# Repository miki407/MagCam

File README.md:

# MagCam

## Introduction
MagCam is a project that aims to bring a better way of teaching principles of magnetism in a classroom environment. Using this device we hope that students will be more engaged in learning about various topics regarding magnetism as well as electromagnetism. During the process of making this device we looked for a way to improve on the traditional methods of displaying magnetic fields.  

## Comparison with traditional methods

|  Method | Presentation | Versatility | Sensitivity | Polarity | Extra Notes |
|---------|--------------|-------------|-------------|----------| ----------- |
| MagCam  | The results can be displayed on a projector | Very versatile in terms of experiments that can be performed | Sensitive to small magnetic fields but limited by the ADC and pre-amp | Has the ability to distinguish between **north** and **south** poles | Can record the data captured
| Iron Dust | Limited number of students can see the results at one time | Number of experiments that can be performed is limited | Only sensitive to strong magnetic fields. Better results can be achieved if particles are suspended in liquid | Doesn't have a way to clearly distinguish between 2 poles | Can stick to the magnets and damage other equipment in the lab |  
| [Flux Detector](https://www.supermagnete.de/eng/school-magnets/flux-detector-small_M-04) | Limited number of students can see the results at one time | Number of experiments that can be performed is sufficient for basic needs | Only sensitive to strong magnetic fields | Doesn't have a way to clearly distinguish between 2 poles |
| Compass array | Limited number of students can see the results at one time |  Very versatile in terms of experiments that can be performed | Sensitive to weak magnetic fields | Has the ability to distinguish between **north** and **south** poles | The device is composed of mechanical compasses and thus needs to be kept horizontal |
| Ferro fluid | Limited number of students can see the results at one time | Number of experiments that can be performed is sufficient for basic needs | Only sensitive to strong magnetic fields | Doesn't have a way to clearly distinguish between 2 poles | Has the possibility to damage other equipment and is hard to clean |
| Virtual demonstration | The results can be displayed on a projector | Any experiment that can be virtually modeled can be performed | The most sensitive option | Has the ability to distinguish between **north** and **south** poles | Requires special training in use of simulation software. It can take a long time for results to be ready. This method doesn't measure magnetic fields and only **simulates** them |

## Basic overview 
MagCam uses 256 hall effect sensors to determine the strength of the magnetic field over a detection area of 110x110 mm. This data is read and sent to the computer for further processing by and esp32 microcontroller. The data is processed and displayed on the computer using an app that was written specifically for this device.

## App
The app reads the values sent by the esp32 and decodes them into individual frames. This data is then calibrated using a baseline value for each sensors. This improves the reading accuracy and allows for less noisy results. In case large gain is used the values received from the device can be averaged. This allows for even less noisy results. 
The app also has a feature that recreates the magnetic field lines from the change in local magnet field strength.
> App is still in development  and more features are planned in the future. There are also plans to improve the gui

## Files
all the files can be found [here](https://github.com/miki407/MagCam)

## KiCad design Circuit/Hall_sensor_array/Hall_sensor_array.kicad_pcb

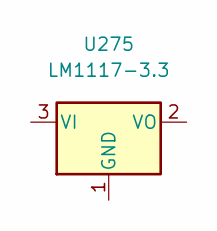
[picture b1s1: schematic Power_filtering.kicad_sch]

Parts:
U275: LM1117-3.3

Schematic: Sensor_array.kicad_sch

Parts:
C1, C2, C3, C4, C5, C6, C7, C8, C9, C10, C11, C12, C13, C14, C15, C16, C17, C18, C19, C20, C21, C22, C23, C24, C25, C26, C27, C28, C29, C30, C31, C32, C33, C34, C35, C36, C37, C38, C39, C40, C41, C42, C43, C44, C45, C46, C47, C48, C49, C50, C51, C52, C53, C54, C55, C56, C57, C58, C59, C60, C61, C62, C63, C64, C65, C66, C67, C68, C69, C70, C71, C72, C73, C74, C75, C76, C77, C78, C79, C80, C81, C82, C83, C84, C85, C86, C87, C88, C89, C90, C91, C92, C93, C94, C95, C96, C97, C98, C99, C100, C101, C102, C103, C104, C105, C106, C107, C108, C109, C110, C111, C112, C113, C114, C115, C116, C117, C118, C119, C120, C121, C122, C123, C124, C125, C126, C127, C128, C129, C130, C131, C132, C133, C134, C135, C136, C137, C138, C139, C140, C141, C142, C143, C144, C145, C146, C147, C148, C149, C150, C151, C152, C153, C154, C155, C156, C157, C158, C159, C160, C161, C162, C163, C164, C165, C166, C167, C168, C169, C170, C171, C172, C173, C174, C175, C176, C177, C178, C179, C180, C181, C182, C183, C184, C185, C186, C187, C188, C189, C190, C191, C192, C193, C194, C195, C196, C197, C198, C199, C200, C201, C202, C203, C204, C205, C206, C207, C208, C209, C210, C211, C212, C213, C214, C215, C216, C217, C218, C219, C220, C221, C222, C223, C224, C225, C226, C227, C228, C229, C230, C231, C232, C233, C234, C235, C236, C237, C238, C239, C240, C241, C242, C243, C244, C245, C246, C247, C248, C249, C250, C251, C252, C253, C254, C255, C256: 100p; C_0603_1608Metric
U1, U2, U3, U4, U5, U6, U7, U8, U9, U10, U11, U12, U13, U14, U15, U16, U17, U18, U19, U20, U21, U22, U23, U24, U25, U26, U27, U28, U29, U30, U31, U32, U33, U34, U35, U36, U37, U38, U39, U40, U41, U42, U43, U44, U45, U46, U47, U48, U49, U50, U51, U52, U53, U54, U55, U56, U57, U58, U59, U60, U61, U62, U63, U64, U65, U66, U67, U68, U69, U70, U71, U72, U73, U74, U75, U76, U77, U78, U79, U80, U81, U82, U83, U84, U85, U86, U87, U88, U89, U90, U91, U92, U93, U94, U95, U96, U97, U98, U99, U100, U101, U102, U103, U104, U105, U106, U107, U108, U109, U110, U111, U112, U113, U114, U115, U116, U117, U118, U119, U120, U121, U122, U123, U124, U125, U126, U127, U128, U129, U130, U131, U132, U133, U134, U135, U136, U137, U138, U139, U140, U141, U142, U143, U144, U145, U146, U147, U148, U149, U150, U151, U152, U153, U154, U155, U156, U157, U158, U159, U160, U161, U162, U163, U164, U165, U166, U167, U168, U169, U170, U171, U172, U173, U174, U175, U176, U177, U178, U179, U180, U181, U182, U183, U184, U185, U186, U187, U188, U189, U190, U191, U192, U193, U194, U195, U196, U197, U198, U199, U200, U201, U202, U203, U204, U205, U206, U207, U208, U209, U210, U211, U212, U213, U214, U215, U216, U217, U218, U219, U220, U221, U222, U223, U224, U225, U226, U227, U228, U229, U230, U231, U232, U233, U234, U235, U236, U237, U238, U239, U240, U241, U242, U243, U244, U245, U246, U247, U248, U249, U250, U251, U252, U253, U254, U255, U256: AH49HSC; SOT-23-3

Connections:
+3.3V: U1.1 (VDD), U2.1 (VDD), U3.1 (VDD), U4.1 (VDD), U5.1 (VDD), U6.1 (VDD), U7.1 (VDD), U8.1 (VDD), U9.1 (VDD), U10.1 (VDD), U11.1 (VDD), U12.1 (VDD), U13.1 (VDD), U14.1 (VDD), U15.1 (VDD), U16.1 (VDD), U17.1 (VDD), U18.1 (VDD), U19.1 (VDD), U20.1 (VDD), U21.1 (VDD), U22.1 (VDD), U23.1 (VDD), U24.1 (VDD), U25.1 (VDD), U26.1 (VDD), U27.1 (VDD), U28.1 (VDD), U29.1 (VDD), U30.1 (VDD), U31.1 (VDD), U32.1 (VDD), U33.1 (VDD), U34.1 (VDD), U35.1 (VDD), U36.1 (VDD), U37.1 (VDD), U38.1 (VDD), U39.1 (VDD), U40.1 (VDD), U41.1 (VDD), U42.1 (VDD), U43.1 (VDD), U44.1 (VDD), U45.1 (VDD), U46.1 (VDD), U47.1 (VDD), U48.1 (VDD), U49.1 (VDD), U50.1 (VDD), U51.1 (VDD), U52.1 (VDD), U53.1 (VDD), U54.1 (VDD), U55.1 (VDD), U56.1 (VDD), U57.1 (VDD), U58.1 (VDD), U59.1 (VDD), U60.1 (VDD), U61.1 (VDD), U62.1 (VDD), U63.1 (VDD), U64.1 (VDD), U65.1 (VDD), U66.1 (VDD), U67.1 (VDD), U68.1 (VDD), U69.1 (VDD), U70.1 (VDD), U71.1 (VDD), U72.1 (VDD), U73.1 (VDD), U74.1 (VDD), U75.1 (VDD), U76.1 (VDD), U77.1 (VDD), U78.1 (VDD), U79.1 (VDD), U80.1 (VDD), U81.1 (VDD), U82.1 (VDD), U83.1 (VDD), U84.1 (VDD), U85.1 (VDD), U86.1 (VDD), U87.1 (VDD), U88.1 (VDD), U89.1 (VDD), U90.1 (VDD), U91.1 (VDD), U92.1 (VDD), U93.1 (VDD), U94.1 (VDD), U95.1 (VDD), U96.1 (VDD), U97.1 (VDD), U98.1 (VDD), U99.1 (VDD), U100.1 (VDD), U101.1 (VDD), U102.1 (VDD), U103.1 (VDD), U104.1 (VDD), U105.1 (VDD), U106.1 (VDD), U107.1 (VDD), U108.1 (VDD), U109.1 (VDD), U110.1 (VDD), U111.1 (VDD), U112.1 (VDD), U113.1 (VDD), U114.1 (VDD), U115.1 (VDD), U116.1 (VDD), U117.1 (VDD), U118.1 (VDD), U119.1 (VDD), U120.1 (VDD), U121.1 (VDD), U122.1 (VDD), U123.1 (VDD), U124.1 (VDD), U125.1 (VDD), U126.1 (VDD), U127.1 (VDD), U128.1 (VDD), U129.1 (VDD), U130.1 (VDD), U131.1 (VDD), U132.1 (VDD), U133.1 (VDD), U134.1 (VDD), U135.1 (VDD), U136.1 (VDD), U137.1 (VDD), U138.1 (VDD), U139.1 (VDD), U140.1 (VDD), U141.1 (VDD), U142.1 (VDD), U143.1 (VDD), U144.1 (VDD), U145.1 (VDD), U146.1 (VDD), U147.1 (VDD), U148.1 (VDD), U149.1 (VDD), U150.1 (VDD), U151.1 (VDD), U152.1 (VDD), U153.1 (VDD), U154.1 (VDD), U155.1 (VDD), U156.1 (VDD), U157.1 (VDD), U158.1 (VDD), U159.1 (VDD), U160.1 (VDD), U161.1 (VDD), U162.1 (VDD), U163.1 (VDD), U164.1 (VDD), U165.1 (VDD), U166.1 (VDD), U167.1 (VDD), U168.1 (VDD), U169.1 (VDD), U170.1 (VDD), U171.1 (VDD), U172.1 (VDD), U173.1 (VDD), U174.1 (VDD), U175.1 (VDD), U176.1 (VDD), U177.1 (VDD), U178.1 (VDD), U179.1 (VDD), U180.1 (VDD), U181.1 (VDD), U182.1 (VDD), U183.1 (VDD), U184.1 (VDD), U185.1 (VDD), U186.1 (VDD), U187.1 (VDD), U188.1 (VDD), U189.1 (VDD), U190.1 (VDD), U191.1 (VDD), U192.1 (VDD), U193.1 (VDD), U194.1 (VDD), U195.1 (VDD), U196.1 (VDD), U197.1 (VDD), U198.1 (VDD), U199.1 (VDD), U200.1 (VDD), U201.1 (VDD), U202.1 (VDD), U203.1 (VDD), U204.1 (VDD), U205.1 (VDD), U206.1 (VDD), U207.1 (VDD), U208.1 (VDD), U209.1 (VDD), U210.1 (VDD), U211.1 (VDD), U212.1 (VDD), U213.1 (VDD), U214.1 (VDD), U215.1 (VDD), U216.1 (VDD), U217.1 (VDD), U218.1 (VDD), U219.1 (VDD), U220.1 (VDD), U221.1 (VDD), U222.1 (VDD), U223.1 (VDD), U224.1 (VDD), U225.1 (VDD), U226.1 (VDD), U227.1 (VDD), U228.1 (VDD), U229.1 (VDD), U230.1 (VDD), U231.1 (VDD), U232.1 (VDD), U233.1 (VDD), U234.1 (VDD), U235.1 (VDD), U236.1 (VDD), U237.1 (VDD), U238.1 (VDD), U239.1 (VDD), U240.1 (VDD), U241.1 (VDD), U242.1 (VDD), U243.1 (VDD), U244.1 (VDD), U245.1 (VDD), U246.1 (VDD), U247.1 (VDD), U248.1 (VDD), U249.1 (VDD), U250.1 (VDD), U251.1 (VDD), U252.1 (VDD), U253.1 (VDD), U254.1 (VDD), U255.1 (VDD), U256.1 (VDD)
GND: C1.2, C2.2, C3.2, C4.2, C5.2, C6.2, C7.2, C8.2, C9.2, C10.2, C11.2, C12.2, C13.2, C14.2, C15.2, C16.2, C17.2, C18.2, C19.2, C20.2, C21.2, C22.2, C23.2, C24.2, C25.2, C26.2, C27.2, C28.2, C29.2, C30.2, C31.2, C32.2, C33.2, C34.2, C35.2, C36.2, C37.2, C38.2, C39.2, C40.2, C41.2, C42.2, C43.2, C44.2, C45.2, C46.2, C47.2, C48.2, C49.2, C50.2, C51.2, C52.2, C53.2, C54.2, C55.2, C56.2, C57.2, C58.2, C59.2, C60.2, C61.2, C62.2, C63.2, C64.2, C65.2, C66.2, C67.2, C68.2, C69.2, C70.2, C71.2, C72.2, C73.2, C74.2, C75.2, C76.2, C77.2, C78.2, C79.2, C80.2, C81.2, C82.2, C83.2, C84.2, C85.2, C86.2, C87.2, C88.2, C89.2, C90.2, C91.2, C92.2, C93.2, C94.2, C95.2, C96.2, C97.2, C98.2, C99.2, C100.2, C101.2, C102.2, C103.2, C104.2, C105.2, C106.2, C107.2, C108.2, C109.2, C110.2, C111.2, C112.2, C113.2, C114.2, C115.2, C116.2, C117.2, C118.2, C119.2, C120.2, C121.2, C122.2, C123.2, C124.2, C125.2, C126.2, C127.2, C128.2, C129.2, C130.2, C131.2, C132.2, C133.2, C134.2, C135.2, C136.2, C137.2, C138.2, C139.2, C140.2, C141.2, C142.2, C143.2, C144.2, C145.2, C146.2, C147.2, C148.2, C149.2, C150.2, C151.2, C152.2, C153.2, C154.2, C155.2, C156.2, C157.2, C158.2, C159.2, C160.2, C161.2, C162.2, C163.2, C164.2, C165.2, C166.2, C167.2, C168.2, C169.2, C170.2, C171.2, C172.2, C173.2, C174.2, C175.2, C176.2, C177.2, C178.2, C179.2, C180.2, C181.2, C182.2, C183.2, C184.2, C185.2, C186.2, C187.2, C188.2, C189.2, C190.2, C191.2, C192.2, C193.2, C194.2, C195.2, C196.2, C197.2, C198.2, C199.2, C200.2, C201.2, C202.2, C203.2, C204.2, C205.2, C206.2, C207.2, C208.2, C209.2, C210.2, C211.2, C212.2, C213.2, C214.2, C215.2, C216.2, C217.2, C218.2, C219.2, C220.2, C221.2, C222.2, C223.2, C224.2, C225.2, C226.2, C227.2, C228.2, C229.2, C230.2, C231.2, C232.2, C233.2, C234.2, C235.2, C236.2, C237.2, C238.2, C239.2, C240.2, C241.2, C242.2, C243.2, C244.2, C245.2, C246.2, C247.2, C248.2, C249.2, C250.2, C251.2, C252.2, C253.2, C254.2, C255.2, C256.2, U1.3 (GND), U2.3 (GND), U3.3 (GND), U4.3 (GND), U5.3 (GND), U6.3 (GND), U7.3 (GND), U8.3 (GND), U9.3 (GND), U10.3 (GND), U11.3 (GND), U12.3 (GND), U13.3 (GND), U14.3 (GND), U15.3 (GND), U16.3 (GND), U17.3 (GND), U18.3 (GND), U19.3 (GND), U20.3 (GND), U21.3 (GND), U22.3 (GND), U23.3 (GND), U24.3 (GND), U25.3 (GND), U26.3 (GND), U27.3 (GND), U28.3 (GND), U29.3 (GND), U30.3 (GND), U31.3 (GND), U32.3 (GND), U33.3 (GND), U34.3 (GND), U35.3 (GND), U36.3 (GND), U37.3 (GND), U38.3 (GND), U39.3 (GND), U40.3 (GND), U41.3 (GND), U42.3 (GND), U43.3 (GND), U44.3 (GND), U45.3 (GND), U46.3 (GND), U47.3 (GND), U48.3 (GND), U49.3 (GND), U50.3 (GND), U51.3 (GND), U52.3 (GND), U53.3 (GND), U54.3 (GND), U55.3 (GND), U56.3 (GND), U57.3 (GND), U58.3 (GND), U59.3 (GND), U60.3 (GND), U61.3 (GND), U62.3 (GND), U63.3 (GND), U64.3 (GND), U65.3 (GND), U66.3 (GND), U67.3 (GND), U68.3 (GND), U69.3 (GND), U70.3 (GND), U71.3 (GND), U72.3 (GND), U73.3 (GND), U74.3 (GND), U75.3 (GND), U76.3 (GND), U77.3 (GND), U78.3 (GND), U79.3 (GND), U80.3 (GND), U81.3 (GND), U82.3 (GND), U83.3 (GND), U84.3 (GND), U85.3 (GND), U86.3 (GND), U87.3 (GND), U88.3 (GND), U89.3 (GND), U90.3 (GND), U91.3 (GND), U92.3 (GND), U93.3 (GND), U94.3 (GND), U95.3 (GND), U96.3 (GND), U97.3 (GND), U98.3 (GND), U99.3 (GND), U100.3 (GND), U101.3 (GND), U102.3 (GND), U103.3 (GND), U104.3 (GND), U105.3 (GND), U106.3 (GND), U107.3 (GND), U108.3 (GND), U109.3 (GND), U110.3 (GND), U111.3 (GND), U112.3 (GND), U113.3 (GND), U114.3 (GND), U115.3 (GND), U116.3 (GND), U117.3 (GND), U118.3 (GND), U119.3 (GND), U120.3 (GND), U121.3 (GND), U122.3 (GND), U123.3 (GND), U124.3 (GND), U125.3 (GND), U126.3 (GND), U127.3 (GND), U128.3 (GND), U129.3 (GND), U130.3 (GND), U131.3 (GND), U132.3 (GND), U133.3 (GND), U134.3 (GND), U135.3 (GND), U136.3 (GND), U137.3 (GND), U138.3 (GND), U139.3 (GND), U140.3 (GND), U141.3 (GND), U142.3 (GND), U143.3 (GND), U144.3 (GND), U145.3 (GND), U146.3 (GND), U147.3 (GND), U148.3 (GND), U149.3 (GND), U150.3 (GND), U151.3 (GND), U152.3 (GND), U153.3 (GND), U154.3 (GND), U155.3 (GND), U156.3 (GND), U157.3 (GND), U158.3 (GND), U159.3 (GND), U160.3 (GND), U161.3 (GND), U162.3 (GND), U163.3 (GND), U164.3 (GND), U165.3 (GND), U166.3 (GND), U167.3 (GND), U168.3 (GND), U169.3 (GND), U170.3 (GND), U171.3 (GND), U172.3 (GND), U173.3 (GND), U174.3 (GND), U175.3 (GND), U176.3 (GND), U177.3 (GND), U178.3 (GND), U179.3 (GND), U180.3 (GND), U181.3 (GND), U182.3 (GND), U183.3 (GND), U184.3 (GND), U185.3 (GND), U186.3 (GND), U187.3 (GND), U188.3 (GND), U189.3 (GND), U190.3 (GND), U191.3 (GND), U192.3 (GND), U193.3 (GND), U194.3 (GND), U195.3 (GND), U196.3 (GND), U197.3 (GND), U198.3 (GND), U199.3 (GND), U200.3 (GND), U201.3 (GND), U202.3 (GND), U203.3 (GND), U204.3 (GND), U205.3 (GND), U206.3 (GND), U207.3 (GND), U208.3 (GND), U209.3 (GND), U210.3 (GND), U211.3 (GND), U212.3 (GND), U213.3 (GND), U214.3 (GND), U215.3 (GND), U216.3 (GND), U217.3 (GND), U218.3 (GND), U219.3 (GND), U220.3 (GND), U221.3 (GND), U222.3 (GND), U223.3 (GND), U224.3 (GND), U225.3 (GND), U226.3 (GND), U227.3 (GND), U228.3 (GND), U229.3 (GND), U230.3 (GND), U231.3 (GND), U232.3 (GND), U233.3 (GND), U234.3 (GND), U235.3 (GND), U236.3 (GND), U237.3 (GND), U238.3 (GND), U239.3 (GND), U240.3 (GND), U241.3 (GND), U242.3 (GND), U243.3 (GND), U244.3 (GND), U245.3 (GND), U246.3 (GND), U247.3 (GND), U248.3 (GND), U249.3 (GND), U250.3 (GND), U251.3 (GND), U252.3 (GND), U253.3 (GND), U254.3 (GND), U255.3 (GND), U256.3 (GND); also elsewhere on the board
X1Y1: C1.1, U1.2 (OUTPUT); also elsewhere on the board
X1Y2: C2.1, U2.2 (OUTPUT); also elsewhere on the board
X1Y3: C3.1, U3.2 (OUTPUT); also elsewhere on the board
X1Y4: C4.1, U4.2 (OUTPUT); also elsewhere on the board
X1Y5: C5.1, U5.2 (OUTPUT); also elsewhere on the board
X1Y6: C6.1, U6.2 (OUTPUT); also elsewhere on the board
X1Y7: C7.1, U7.2 (OUTPUT); also elsewhere on the board
X1Y8: C8.1, U8.2 (OUTPUT); also elsewhere on the board
X1Y9: C9.1, U9.2 (OUTPUT); also elsewhere on the board
X1Y10: C10.1, U10.2 (OUTPUT); also elsewhere on the board
X1Y11: C11.1, U11.2 (OUTPUT); also elsewhere on the board
X1Y12: C12.1, U12.2 (OUTPUT); also elsewhere on the board
X1Y13: C13.1, U13.2 (OUTPUT); also elsewhere on the board
X1Y14: C14.1, U14.2 (OUTPUT); also elsewhere on the board
X1Y15: C15.1, U15.2 (OUTPUT); also elsewhere on the board
X1Y16: C16.1, U16.2 (OUTPUT); also elsewhere on the board
X2Y1: C17.1, U17.2 (OUTPUT); also elsewhere on the board
X2Y2: C18.1, U18.2 (OUTPUT); also elsewhere on the board
X2Y3: C19.1, U19.2 (OUTPUT); also elsewhere on the board
X2Y4: C20.1, U20.2 (OUTPUT); also elsewhere on the board
X2Y5: C21.1, U21.2 (OUTPUT); also elsewhere on the board
X2Y6: C22.1, U22.2 (OUTPUT); also elsewhere on the board
X2Y7: C23.1, U23.2 (OUTPUT); also elsewhere on the board
X2Y8: C24.1, U24.2 (OUTPUT); also elsewhere on the board
X2Y9: C25.1, U25.2 (OUTPUT); also elsewhere on the board
X2Y10: C26.1, U26.2 (OUTPUT); also elsewhere on the board
X2Y11: C27.1, U27.2 (OUTPUT); also elsewhere on the board
X2Y12: C28.1, U28.2 (OUTPUT); also elsewhere on the board
X2Y13: C29.1, U29.2 (OUTPUT); also elsewhere on the board
X2Y14: C30.1, U30.2 (OUTPUT); also elsewhere on the board
X2Y15: C31.1, U31.2 (OUTPUT); also elsewhere on the board
X2Y16: C32.1, U32.2 (OUTPUT); also elsewhere on the board
X3Y1: C33.1, U33.2 (OUTPUT); also elsewhere on the board
X3Y2: C34.1, U34.2 (OUTPUT); also elsewhere on the board
X3Y3: C35.1, U35.2 (OUTPUT); also elsewhere on the board
X3Y4: C36.1, U36.2 (OUTPUT); also elsewhere on the board
X3Y5: C37.1, U37.2 (OUTPUT); also elsewhere on the board
X3Y6: C38.1, U38.2 (OUTPUT); also elsewhere on the board
X3Y7: C39.1, U39.2 (OUTPUT); also elsewhere on the board
X3Y8: C40.1, U40.2 (OUTPUT); also elsewhere on the board
X3Y9: C41.1, U41.2 (OUTPUT); also elsewhere on the board
X3Y10: C42.1, U42.2 (OUTPUT); also elsewhere on the board
X3Y11: C43.1, U43.2 (OUTPUT); also elsewhere on the board
X3Y12: C44.1, U44.2 (OUTPUT); also elsewhere on the board
X3Y13: C45.1, U45.2 (OUTPUT); also elsewhere on the board
X3Y14: C46.1, U46.2 (OUTPUT); also elsewhere on the board
X3Y15: C47.1, U47.2 (OUTPUT); also elsewhere on the board
X3Y16: C48.1, U48.2 (OUTPUT); also elsewhere on the board
X4Y1: C49.1, U49.2 (OUTPUT); also elsewhere on the board
X4Y2: C50.1, U50.2 (OUTPUT); also elsewhere on the board
X4Y3: C51.1, U51.2 (OUTPUT); also elsewhere on the board
X4Y4: C52.1, U52.2 (OUTPUT); also elsewhere on the board
X4Y5: C53.1, U53.2 (OUTPUT); also elsewhere on the board
X4Y6: C54.1, U54.2 (OUTPUT); also elsewhere on the board
X4Y7: C55.1, U55.2 (OUTPUT); also elsewhere on the board
X4Y8: C56.1, U56.2 (OUTPUT); also elsewhere on the board
X4Y9: C57.1, U57.2 (OUTPUT); also elsewhere on the board
X4Y10: C58.1, U58.2 (OUTPUT); also elsewhere on the board
X4Y11: C59.1, U59.2 (OUTPUT); also elsewhere on the board
X4Y12: C60.1, U60.2 (OUTPUT); also elsewhere on the board
X4Y13: C61.1, U61.2 (OUTPUT); also elsewhere on the board
X4Y14: C62.1, U62.2 (OUTPUT); also elsewhere on the board
X4Y15: C63.1, U63.2 (OUTPUT); also elsewhere on the board
X4Y16: C64.1, U64.2 (OUTPUT); also elsewhere on the board
X5Y1: C65.1, U65.2 (OUTPUT); also elsewhere on the board
X5Y2: C66.1, U66.2 (OUTPUT); also elsewhere on the board
X5Y3: C67.1, U67.2 (OUTPUT); also elsewhere on the board
X5Y4: C68.1, U68.2 (OUTPUT); also elsewhere on the board
X5Y5: C69.1, U69.2 (OUTPUT); also elsewhere on the board
X5Y6: C70.1, U70.2 (OUTPUT); also elsewhere on the board
X5Y7: C71.1, U71.2 (OUTPUT); also elsewhere on the board
X5Y8: C72.1, U72.2 (OUTPUT); also elsewhere on the board
X5Y9: C73.1, U73.2 (OUTPUT); also elsewhere on the board
X5Y10: C74.1, U74.2 (OUTPUT); also elsewhere on the board
X5Y11: C75.1, U75.2 (OUTPUT); also elsewhere on the board
X5Y12: C76.1, U76.2 (OUTPUT); also elsewhere on the board
X5Y13: C77.1, U77.2 (OUTPUT); also elsewhere on the board
X5Y14: C78.1, U78.2 (OUTPUT); also elsewhere on the board
X5Y15: C79.1, U79.2 (OUTPUT); also elsewhere on the board
X5Y16: C80.1, U80.2 (OUTPUT); also elsewhere on the board
X6Y1: C81.1, U81.2 (OUTPUT); also elsewhere on the board
X6Y2: C82.1, U82.2 (OUTPUT); also elsewhere on the board
X6Y3: C83.1, U83.2 (OUTPUT); also elsewhere on the board
X6Y4: C84.1, U84.2 (OUTPUT); also elsewhere on the board
X6Y5: C85.1, U85.2 (OUTPUT); also elsewhere on the board
X6Y6: C86.1, U86.2 (OUTPUT); also elsewhere on the board
X6Y7: C87.1, U87.2 (OUTPUT); also elsewhere on the board
X6Y8: C88.1, U88.2 (OUTPUT); also elsewhere on the board
X6Y9: C89.1, U89.2 (OUTPUT); also elsewhere on the board
X6Y10: C90.1, U90.2 (OUTPUT); also elsewhere on the board
X6Y11: C91.1, U91.2 (OUTPUT); also elsewhere on the board
X6Y12: C92.1, U92.2 (OUTPUT); also elsewhere on the board
X6Y13: C93.1, U93.2 (OUTPUT); also elsewhere on the board
X6Y14: C94.1, U94.2 (OUTPUT); also elsewhere on the board
X6Y15: C95.1, U95.2 (OUTPUT); also elsewhere on the board
X6Y16: C96.1, U96.2 (OUTPUT); also elsewhere on the board
X7Y1: C97.1, U97.2 (OUTPUT); also elsewhere on the board
X7Y2: C98.1, U98.2 (OUTPUT); also elsewhere on the board
X7Y3: C99.1, U99.2 (OUTPUT); also elsewhere on the board
X7Y4: C100.1, U100.2 (OUTPUT); also elsewhere on the board
X7Y5: C101.1, U101.2 (OUTPUT); also elsewhere on the board
X7Y6: C102.1, U102.2 (OUTPUT); also elsewhere on the board
X7Y7: C103.1, U103.2 (OUTPUT); also elsewhere on the board
X7Y8: C104.1, U104.2 (OUTPUT); also elsewhere on the board
X7Y9: C105.1, U105.2 (OUTPUT); also elsewhere on the board
X7Y10: C106.1, U106.2 (OUTPUT); also elsewhere on the board
X7Y11: C107.1, U107.2 (OUTPUT); also elsewhere on the board
X7Y12: C108.1, U108.2 (OUTPUT); also elsewhere on the board
X7Y13: C109.1, U109.2 (OUTPUT); also elsewhere on the board
X7Y14: C110.1, U110.2 (OUTPUT); also elsewhere on the board
X7Y15: C111.1, U111.2 (OUTPUT); also elsewhere on the board
X7Y16: C112.1, U112.2 (OUTPUT); also elsewhere on the board
X8Y1: C113.1, U113.2 (OUTPUT); also elsewhere on the board
X8Y2: C114.1, U114.2 (OUTPUT); also elsewhere on the board
X8Y3: C115.1, U115.2 (OUTPUT); also elsewhere on the board
X8Y4: C116.1, U116.2 (OUTPUT); also elsewhere on the board
X8Y5: C117.1, U117.2 (OUTPUT); also elsewhere on the board
X8Y6: C118.1, U118.2 (OUTPUT); also elsewhere on the board
X8Y7: C119.1, U119.2 (OUTPUT); also elsewhere on the board
X8Y8: C120.1, U120.2 (OUTPUT); also elsewhere on the board
X8Y9: C121.1, U121.2 (OUTPUT); also elsewhere on the board
X8Y10: C122.1, U122.2 (OUTPUT); also elsewhere on the board
X8Y11: C123.1, U123.2 (OUTPUT); also elsewhere on the board
X8Y12: C124.1, U124.2 (OUTPUT); also elsewhere on the board
X8Y13: C125.1, U125.2 (OUTPUT); also elsewhere on the board
X8Y14: C126.1, U126.2 (OUTPUT); also elsewhere on the board
X8Y15: C127.1, U127.2 (OUTPUT); also elsewhere on the board
X8Y16: C128.1, U128.2 (OUTPUT); also elsewhere on the board
X9Y1: C129.1, U129.2 (OUTPUT); also elsewhere on the board
X9Y2: C130.1, U130.2 (OUTPUT); also elsewhere on the board
X9Y3: C131.1, U131.2 (OUTPUT); also elsewhere on the board
X9Y4: C132.1, U132.2 (OUTPUT); also elsewhere on the board
X9Y5: C133.1, U133.2 (OUTPUT); also elsewhere on the board
X9Y6: C134.1, U134.2 (OUTPUT); also elsewhere on the board
X9Y7: C135.1, U135.2 (OUTPUT); also elsewhere on the board
X9Y8: C136.1, U136.2 (OUTPUT); also elsewhere on the board
X9Y9: C137.1, U137.2 (OUTPUT); also elsewhere on the board
X9Y10: C138.1, U138.2 (OUTPUT); also elsewhere on the board
X9Y11: C139.1, U139.2 (OUTPUT); also elsewhere on the board
X9Y12: C140.1, U140.2 (OUTPUT); also elsewhere on the board
X9Y13: C141.1, U141.2 (OUTPUT); also elsewhere on the board
X9Y14: C142.1, U142.2 (OUTPUT); also elsewhere on the board
X9Y15: C143.1, U143.2 (OUTPUT); also elsewhere on the board
X9Y16: C144.1, U144.2 (OUTPUT); also elsewhere on the board
X10Y1: C145.1, U145.2 (OUTPUT); also elsewhere on the board
X10Y2: C146.1, U146.2 (OUTPUT); also elsewhere on the board
X10Y3: C147.1, U147.2 (OUTPUT); also elsewhere on the board
X10Y4: C148.1, U148.2 (OUTPUT); also elsewhere on the board
X10Y5: C149.1, U149.2 (OUTPUT); also elsewhere on the board
X10Y6: C150.1, U150.2 (OUTPUT); also elsewhere on the board
X10Y7: C151.1, U151.2 (OUTPUT); also elsewhere on the board
X10Y8: C152.1, U152.2 (OUTPUT); also elsewhere on the board
X10Y9: C153.1, U153.2 (OUTPUT); also elsewhere on the board
X10Y10: C154.1, U154.2 (OUTPUT); also elsewhere on the board
X10Y11: C155.1, U155.2 (OUTPUT); also elsewhere on the board
X10Y12: C156.1, U156.2 (OUTPUT); also elsewhere on the board
X10Y13: C157.1, U157.2 (OUTPUT); also elsewhere on the board
X10Y14: C158.1, U158.2 (OUTPUT); also elsewhere on the board
X10Y15: C159.1, U159.2 (OUTPUT); also elsewhere on the board
X10Y16: C160.1, U160.2 (OUTPUT); also elsewhere on the board
X11Y1: C161.1, U161.2 (OUTPUT); also elsewhere on the board
X11Y2: C162.1, U162.2 (OUTPUT); also elsewhere on the board
X11Y3: C163.1, U163.2 (OUTPUT); also elsewhere on the board
X11Y4: C164.1, U164.2 (OUTPUT); also elsewhere on the board
X11Y5: C165.1, U165.2 (OUTPUT); also elsewhere on the board
X11Y6: C166.1, U166.2 (OUTPUT); also elsewhere on the board
X11Y7: C167.1, U167.2 (OUTPUT); also elsewhere on the board
X11Y8: C168.1, U168.2 (OUTPUT); also elsewhere on the board
X11Y9: C169.1, U169.2 (OUTPUT); also elsewhere on the board
X11Y10: C170.1, U170.2 (OUTPUT); also elsewhere on the board
X11Y11: C171.1, U171.2 (OUTPUT); also elsewhere on the board
X11Y12: C172.1, U172.2 (OUTPUT); also elsewhere on the board
X11Y13: C173.1, U173.2 (OUTPUT); also elsewhere on the board
X11Y14: C174.1, U174.2 (OUTPUT); also elsewhere on the board
X11Y15: C175.1, U175.2 (OUTPUT); also elsewhere on the board
X11Y16: C176.1, U176.2 (OUTPUT); also elsewhere on the board
X12Y1: C177.1, U177.2 (OUTPUT); also elsewhere on the board
X12Y2: C178.1, U178.2 (OUTPUT); also elsewhere on the board
X12Y3: C179.1, U179.2 (OUTPUT); also elsewhere on the board
X12Y4: C180.1, U180.2 (OUTPUT); also elsewhere on the board
X12Y5: C181.1, U181.2 (OUTPUT); also elsewhere on the board
X12Y6: C182.1, U182.2 (OUTPUT); also elsewhere on the board
X12Y7: C183.1, U183.2 (OUTPUT); also elsewhere on the board
X12Y8: C184.1, U184.2 (OUTPUT); also elsewhere on the board
X12Y9: C185.1, U185.2 (OUTPUT); also elsewhere on the board
X12Y10: C186.1, U186.2 (OUTPUT); also elsewhere on the board
X12Y11: C187.1, U187.2 (OUTPUT); also elsewhere on the board
X12Y12: C188.1, U188.2 (OUTPUT); also elsewhere on the board
X12Y13: C189.1, U189.2 (OUTPUT); also elsewhere on the board
X12Y14: C190.1, U190.2 (OUTPUT); also elsewhere on the board
X12Y15: C191.1, U191.2 (OUTPUT); also elsewhere on the board
X12Y16: C192.1, U192.2 (OUTPUT); also elsewhere on the board
X13Y1: C193.1, U193.2 (OUTPUT); also elsewhere on the board
X13Y2: C194.1, U194.2 (OUTPUT); also elsewhere on the board
X13Y3: C195.1, U195.2 (OUTPUT); also elsewhere on the board
X13Y4: C196.1, U196.2 (OUTPUT); also elsewhere on the board
X13Y5: C197.1, U197.2 (OUTPUT); also elsewhere on the board
X13Y6: C198.1, U198.2 (OUTPUT); also elsewhere on the board
X13Y7: C199.1, U199.2 (OUTPUT); also elsewhere on the board
X13Y8: C200.1, U200.2 (OUTPUT); also elsewhere on the board
X13Y9: C201.1, U201.2 (OUTPUT); also elsewhere on the board
X13Y10: C202.1, U202.2 (OUTPUT); also elsewhere on the board
X13Y11: C203.1, U203.2 (OUTPUT); also elsewhere on the board
X13Y12: C204.1, U204.2 (OUTPUT); also elsewhere on the board
X13Y13: C205.1, U205.2 (OUTPUT); also elsewhere on the board
X13Y14: C206.1, U206.2 (OUTPUT); also elsewhere on the board
X13Y15: C207.1, U207.2 (OUTPUT); also elsewhere on the board
X13Y16: C208.1, U208.2 (OUTPUT); also elsewhere on the board
X14Y1: C209.1, U209.2 (OUTPUT); also elsewhere on the board
X14Y2: C210.1, U210.2 (OUTPUT); also elsewhere on the board
X14Y3: C211.1, U211.2 (OUTPUT); also elsewhere on the board
X14Y4: C212.1, U212.2 (OUTPUT); also elsewhere on the board
X14Y5: C213.1, U213.2 (OUTPUT); also elsewhere on the board
X14Y6: C214.1, U214.2 (OUTPUT); also elsewhere on the board
X14Y7: C215.1, U215.2 (OUTPUT); also elsewhere on the board
X14Y8: C216.1, U216.2 (OUTPUT); also elsewhere on the board
X14Y9: C217.1, U217.2 (OUTPUT); also elsewhere on the board
X14Y10: C218.1, U218.2 (OUTPUT); also elsewhere on the board
X14Y11: C219.1, U219.2 (OUTPUT); also elsewhere on the board
X14Y12: C220.1, U220.2 (OUTPUT); also elsewhere on the board
X14Y13: C221.1, U221.2 (OUTPUT); also elsewhere on the board
X14Y14: C222.1, U222.2 (OUTPUT); also elsewhere on the board
X14Y15: C223.1, U223.2 (OUTPUT); also elsewhere on the board
X14Y16: C224.1, U224.2 (OUTPUT); also elsewhere on the board
X15Y1: C225.1, U225.2 (OUTPUT); also elsewhere on the board
X15Y2: C226.1, U226.2 (OUTPUT); also elsewhere on the board
X15Y3: C227.1, U227.2 (OUTPUT); also elsewhere on the board
X15Y4: C228.1, U228.2 (OUTPUT); also elsewhere on the board
X15Y5: C229.1, U229.2 (OUTPUT); also elsewhere on the board
X15Y6: C230.1, U230.2 (OUTPUT); also elsewhere on the board
X15Y7: C231.1, U231.2 (OUTPUT); also elsewhere on the board
X15Y8: C232.1, U232.2 (OUTPUT); also elsewhere on the board
X15Y9: C233.1, U233.2 (OUTPUT); also elsewhere on the board
X15Y10: C234.1, U234.2 (OUTPUT); also elsewhere on the board
X15Y11: C235.1, U235.2 (OUTPUT); also elsewhere on the board
X15Y12: C236.1, U236.2 (OUTPUT); also elsewhere on the board
X15Y13: C237.1, U237.2 (OUTPUT); also elsewhere on the board
X15Y14: C238.1, U238.2 (OUTPUT); also elsewhere on the board
X15Y15: C239.1, U239.2 (OUTPUT); also elsewhere on the board
X15Y16: C240.1, U240.2 (OUTPUT); also elsewhere on the board
X16Y1: C241.1, U241.2 (OUTPUT); also elsewhere on the board
X16Y2: C242.1, U242.2 (OUTPUT); also elsewhere on the board
X16Y3: C243.1, U243.2 (OUTPUT); also elsewhere on the board
X16Y4: C244.1, U244.2 (OUTPUT); also elsewhere on the board
X16Y5: C245.1, U245.2 (OUTPUT); also elsewhere on the board
X16Y6: C246.1, U246.2 (OUTPUT); also elsewhere on the board
X16Y7: C247.1, U247.2 (OUTPUT); also elsewhere on the board
X16Y8: C248.1, U248.2 (OUTPUT); also elsewhere on the board
X16Y9: C249.1, U249.2 (OUTPUT); also elsewhere on the board
X16Y10: C250.1, U250.2 (OUTPUT); also elsewhere on the board
X16Y11: C251.1, U251.2 (OUTPUT); also elsewhere on the board
X16Y12: C252.1, U252.2 (OUTPUT); also elsewhere on the board
X16Y13: C253.1, U253.2 (OUTPUT); also elsewhere on the board
X16Y14: C254.1, U254.2 (OUTPUT)
X16Y15: C255.1, U255.2 (OUTPUT)
X16Y16: C256.1, U256.2 (OUTPUT)

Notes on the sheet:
With typical current usage of 2mA minimum current of 1.2mA and max current of 3.2mA. The current usage for the whole array should be around 256 * 2mA = 512mA
Hall_Sensor array 16 x 16 array of hall sensors totaling to 256 individual sensors.
Sensor datasheet: https://datasheet.lcsc.com/lcsc/2004231002_PJSEMI-AH49HSC_C510723.pdf
